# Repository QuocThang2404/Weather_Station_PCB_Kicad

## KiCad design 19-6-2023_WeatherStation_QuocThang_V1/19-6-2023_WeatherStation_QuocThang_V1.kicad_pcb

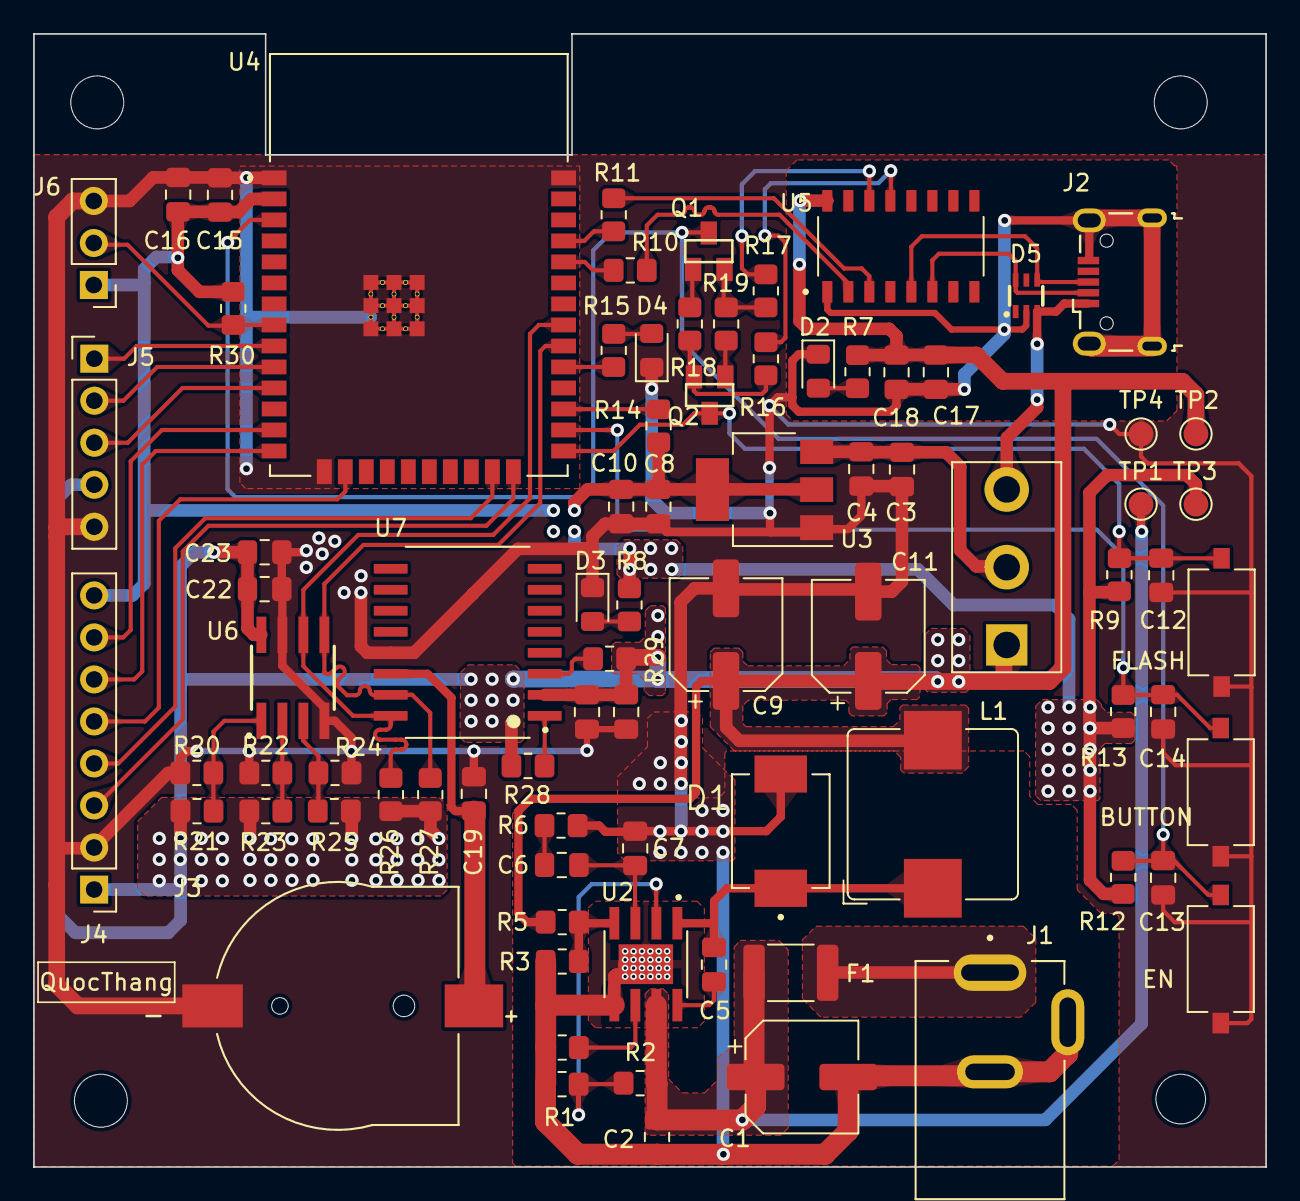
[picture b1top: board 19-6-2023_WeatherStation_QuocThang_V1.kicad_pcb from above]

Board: 2 copper layers, 74.5 x 68.5 mm, 86 parts (0 on the bottom side), 51 nets.

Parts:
BUTTON : SW_Push; SW_Tactile_SPST_NO_Straight_CK_PTS636Sx25SMTRLFS
C1: 47uF; CP_Elec_6.3x5.4
C2: 10uF, 50V; C_0805_2012Metric_Pad1.18x1.45mm_HandSolder
C3, C8, C19, C20, C23: 1uF; C_0805_2012Metric_Pad1.18x1.45mm_HandSolder
C4, C5, C10, C15, C18: 100nF; C_0805_2012Metric_Pad1.18x1.45mm_HandSolder
C6: 150pF; C_0805_2012Metric_Pad1.18x1.45mm_HandSolder
C7: C_Small; C_0805_2012Metric_Pad1.18x1.45mm_HandSolder
C9: 22uF; CP_Elec_6.3x5.4
C11: 47uF; CP_Elec_6.3x7.7
C12, C13, C14: 100nF, 16V; C_0805_2012Metric_Pad1.18x1.45mm_HandSolder
C16, C17: 22uF; C_0805_2012Metric_Pad1.18x1.45mm_HandSolder
C21, C22: 0.1uF; C_0805_2012Metric_Pad1.18x1.45mm_HandSolder
D1: SS34; DIOM7959X265N
D2, D3, D4: LED; LED_0805_2012Metric_Pad1.15x1.40mm_HandSolder
D5: SMF05C; SC70-6
EN: SW_Push; SW_Tactile_SPST_NO_Straight_CK_PTS636Sx25SMTRLFS
F1: Fuse_Small; Fuse_1812_4532Metric_Pad1.30x3.40mm_HandSolder
FLASH: SW_Push; SW_Tactile_SPST_NO_Straight_CK_PTS636Sx25SMTRLFS
H1, H2, H3, H4: MountingHole; MountingHole_3.2mm_M3
J1: DC-005-5A-2.0
J2: USB_B_Micro; USB_Micro-B_Wuerth_629105150521
J3: BC501SM-TR; MPD_BC501SM-TR
J4: Conn_01x08_Pin; PinHeader_1x08_P2.54mm_Vertical
J5: Conn_01x05_Pin; PinHeader_1x05_P2.54mm_Vertical
J6: Conn_01x03_Pin; PinHeader_1x03_P2.54mm_Vertical
L1: 22uH; L_Bourns_SRP1038C_10.0x10.0mm
Q1, Q2: MMBT2222A
R1: 24.9k; R_0805_2012Metric_Pad1.20x1.40mm_HandSolder
R2, R4, R6: 100k; R_0805_2012Metric_Pad1.20x1.40mm_HandSolder
R3: 40.2k; R_0805_2012Metric_Pad1.20x1.40mm_HandSolder
R5: 220k; R_0805_2012Metric_Pad1.20x1.40mm_HandSolder
R7, R8, R15: 1k; R_0805_2012Metric_Pad1.20x1.40mm_HandSolder
R9, R12, R13, R14, R18, R19: 10k; R_0805_2012Metric_Pad1.20x1.40mm_HandSolder
R10, R11, R20, R22, R24: 0; R_0805_2012Metric_Pad1.20x1.40mm_HandSolder
R16, R17: 22; R_0805_2012Metric_Pad1.20x1.40mm_HandSolder
R21, R23, R25, R26, R27, R28, R29, R30: 4.7k; R_0805_2012Metric_Pad1.20x1.40mm_HandSolder
SW4: SS-12D10
TP1, TP2, TP3, TP4: TestPoint; TestPoint_Pad_D1.5mm
U2: MP1584EN-LF-Z; SOIC127P600X170-9N
U3: LM1117MP-3.3; SOT-223-3_TabPin2
U4: ESP32-WROOM-32E_(16MB); XCVR_ESP32-WROOM-32E_(16MB)
U5: CH340C; SOIC127P600X180-16N
U6: CAT24C32WI-GT3
U7: DS3231SN#; DS3231SN

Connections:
+3.3V: C8.2, C10.2, C15.1, C16.1, J4.8, J6.1, R8.1, R9.1, R12.1, R13.1, R14.2, R30.1, TP3.1, U3.2 (VO), U4.2 (3V3)
+5V: C9.1, C11.1, C17.2, C18.1, C20.1, C21.1, C22.1, C23.1, J4.1, J5.4, L1.2, R5.2, R7.1, R21.1, R23.1, R25.1, R26.1, R27.1, R28.1, R29.1, SW4.1 (LEFT), TP2.1, U5.16 (VCC), U6.8 (VCC), U7.2 (VCC)
/USB_To_TTL/D_N: D5.6, J2.2 (D-), U5.6 (UD-)
/USB_To_TTL/D_P: D5.4, J2.3 (D+), U5.5 (UD+)
BUTTON CHECK: BUTTON.1, C14.1, R13.2, U4.26 (IO4)
DTR: Q2.2, R16.1, R18.2
EN: C13.1, EN.1, Q1.3, R12.2, U4.3 (EN)
FLASH: C12.1, FLASH.1, Q2.3, R9.2, U4.25 (IO0)
GND: BUTTON.2, C1.2, C2.2, C3.1, C4.1, C7.1, C8.1, C9.2, C10.1, C11.2, C12.2, C13.2, C14.2, C15.2, C16.2, C17.1, C18.2, C19.2, C20.2, C21.2, C22.2, C23.2, D1.A, D2.1 (K), D3.1 (K), D4.1 (K), D5.2, EN.2, FLASH.2, J1.2, J1.3, J2.5 (GND), J2.6 (Shield), J3.- (NEG), J4.2, J5.5, J6.3, R1.2, R3.2, R4.2, R6.2, R20.1, R22.1, R24.1, TP4.1, U2.5 (GND), U2.9 (EP), U3.1 (GND), U4.1 (GND), U4.15 (GND), U4.38 (GND), U4.39_1 (GND), U4.39_2 (GND), U4.39_3 (GND), U4.39_4 (GND), U4.39_5 (GND), U4.39_6 (GND), U4.39_7 (GND), U4.39_8 (GND), U4.39_9 (GND), U5.1 (GND), U6.4 (VSS), U6.7 (WP), U7.13 (GND)
LED TEST: R15.1, U4.29 (IO5)
unnamed: C6.1, R6.1
unnamed: D2.2 (A), R7.2
unnamed: D3.2 (A), R8.2
unnamed: D4.2 (A), R15.2
unnamed: F1.1, J1.1
unnamed: C19.1, J3.+ (POS), U7.14 (VBAT)
unnamed: Q1.1, R18.1
unnamed: Q2.1, R19.1
unnamed: C3.2, C4.2, SW4.2 (MID), U3.3 (VI)
unnamed: C5.1, U2.8 (BST)
unnamed: C6.2, C7.2, U2.3 (COMP)
unnamed: R1.1, R2.2, U2.2 (EN)
unnamed: R3.1, R5.1, U2.4 (FB)
unnamed: R4.1, U2.6 (FREQ)
unnamed: C5.2, D1.C, L1.1, U2.1 (SW)
unnamed: R14.1, U4.27 (IO16)
unnamed: R10.2, U4.34 (RXD0)
unnamed: R11.2, U4.35 (TXD0)
unnamed: R16.2, U5.13 (~DTR)
unnamed: R17.2, U5.14 (~RTS)
unnamed: R20.2, R21.2, U6.1 (A0)
unnamed: R22.2, R23.2, U6.2 (A1)
unnamed: R24.2, R25.2, U6.3 (A2)
unnamed: R28.2, U7.1 (32KHZ)
unnamed: R29.2, U7.3 (SQW/~INT)
ONE WIRE: J6.2, R30.2, U4.8 (IO32)
Phase A: J5.1, U4.9 (IO33)
Phase B: J5.2, U4.10 (IO25)
RTS: Q1.2, R17.1, R19.2
SCL: R26.2, U4.31 (IO19), U6.6 (SCL), U7.16 (SCL)
SDA: R27.2, U4.30 (IO18), U6.5 (SDA), U7.15 (SDA)
SPI_CS0: J4.4, U4.23 (IO15)
SPI_MOSI: J4.5, U4.16 (IO13)
SPI_RESET: J4.3, U4.24 (IO2)
SPI_RS: J4.6, U4.14 (IO12)
SPI_SCLK: J4.7, U4.13 (IO14)
SW: J5.3, U4.11 (IO26)
U0_N: R10.1, U5.2 (TXD)
U0_P: R11.1, U5.3 (RXD)
V_USB: D5.3, J2.1 (VBUS), SW4.3 (RIGHT)
Vin: C1.1, C2.1, F1.2, R2.1, TP1.1, U2.7 (VIN)

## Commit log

2023-07-08 Done PCB
